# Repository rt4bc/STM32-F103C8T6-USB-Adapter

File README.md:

# STM32-F103C8T6-USB-Adapter
This hardware will be used as an adapter, expand GPIO, I2C, SPI and CAN interface via USB port.

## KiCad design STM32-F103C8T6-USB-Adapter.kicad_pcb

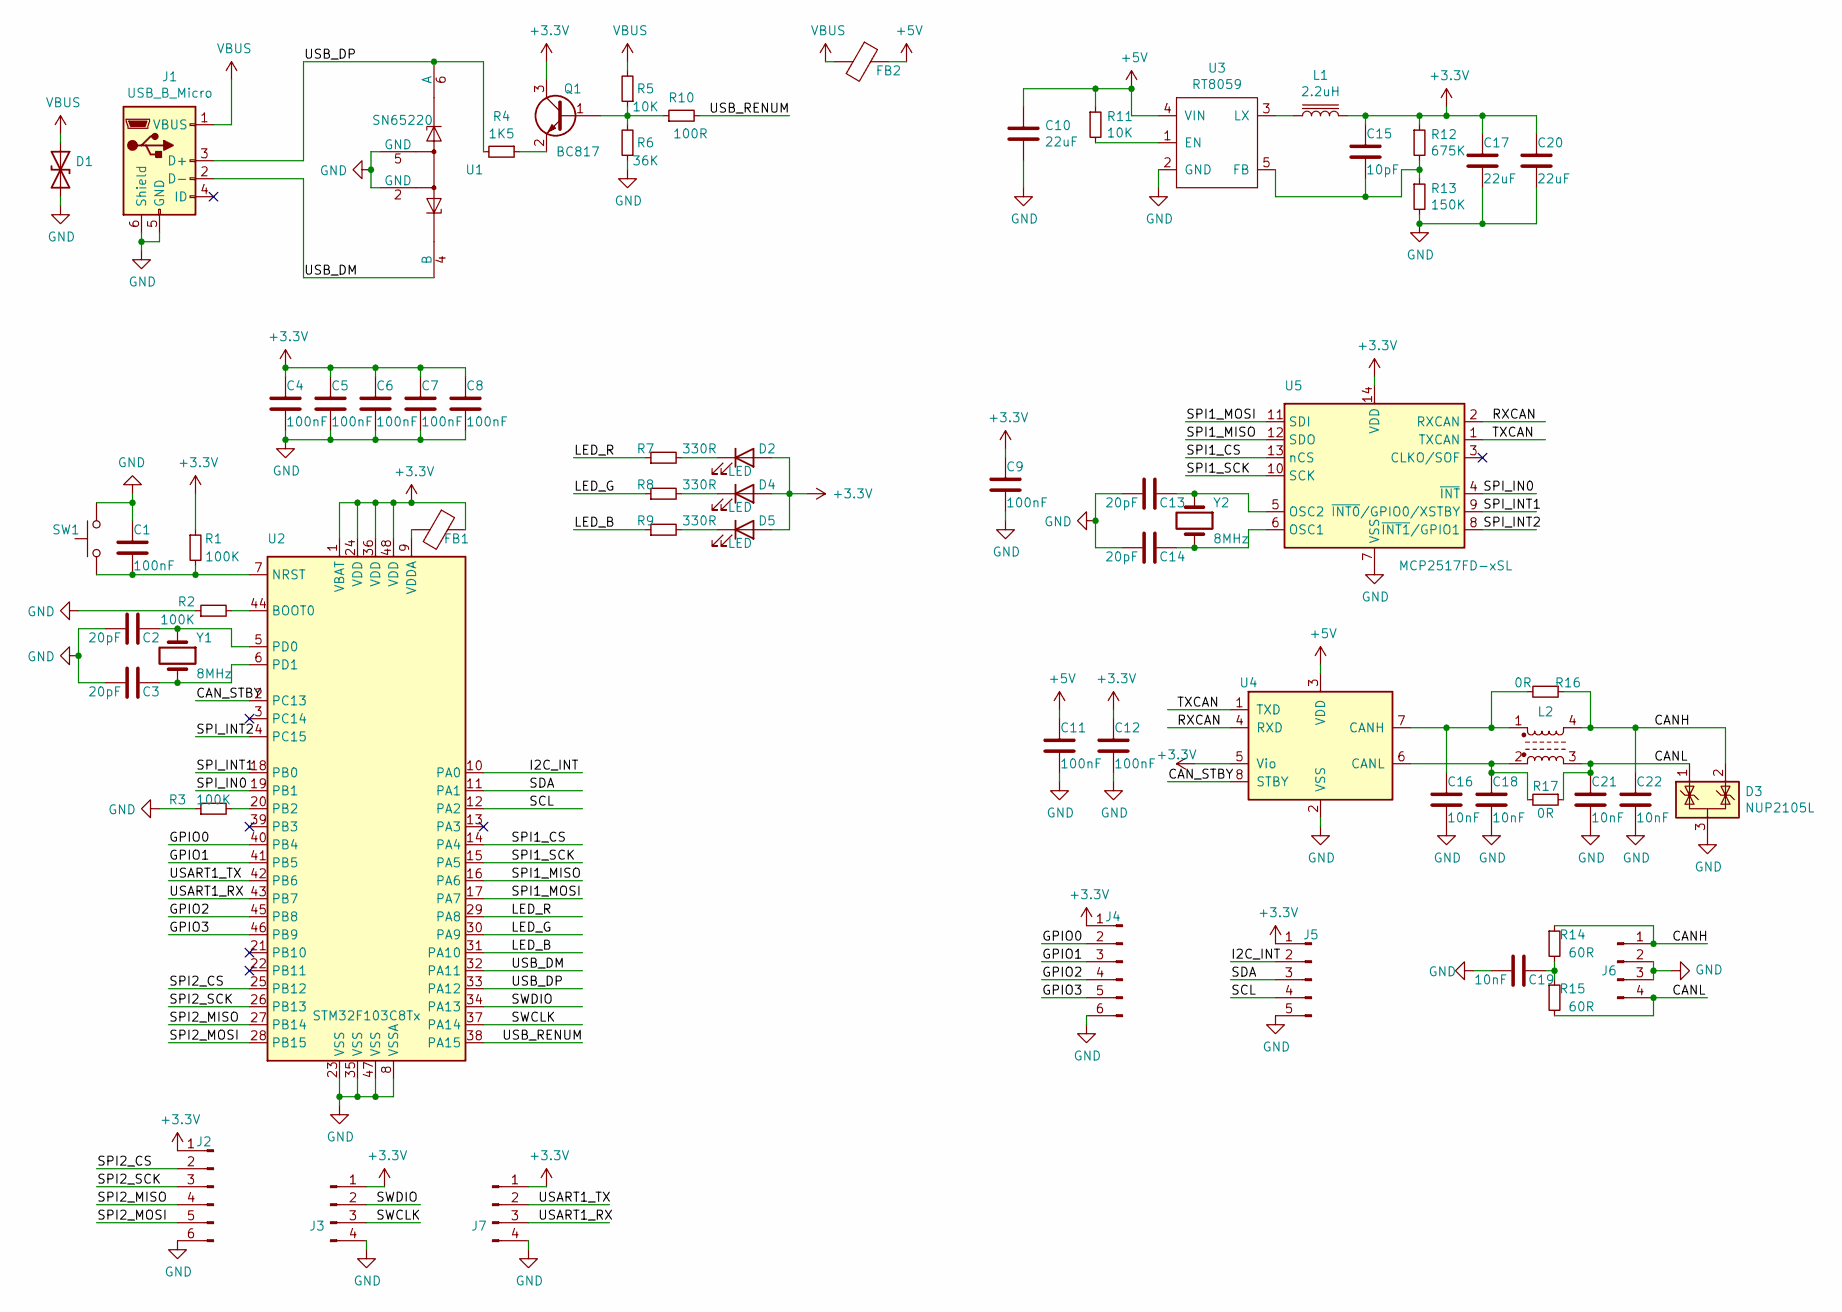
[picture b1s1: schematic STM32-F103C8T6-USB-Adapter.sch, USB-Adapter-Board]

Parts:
C1, C4, C5, C6, C7, C8, C9, C11, C12: 100nF; C_0603_1608Metric_Pad1.08x0.95mm_HandSolder
C2, C3, C13, C14: 20pF; C_0603_1608Metric_Pad1.08x0.95mm_HandSolder
C10, C17, C20: 22uF; C_0805_2012Metric_Pad1.18x1.45mm_HandSolder
C15: 10pF; C_0603_1608Metric_Pad1.08x0.95mm_HandSolder
C16, C18, C19, C21, C22: 10nF; C_0603_1608Metric_Pad1.08x0.95mm_HandSolder
D1: PESD5V0L1BA; D_SOD-323_HandSoldering
D2, D4, D5: LED; LED_0603_1608Metric_Pad1.05x0.95mm_HandSolder
D3: NUP2105L; SOT-23
FB1, FB2: Ferrite_Bead; L_0805_2012Metric_Pad1.05x1.20mm_HandSolder
J1: USB_B_Micro; USB_Mini-B_Wuerth_65100516121_Horizontal
J2, J4: Conn_01x06_Male; PinHeader_1x06_P2.54mm_Vertical
J3, J6, J7: Conn_01x04_Male; PinHeader_1x04_P2.54mm_Vertical
J5: Conn_01x05_Male; PinHeader_1x05_P2.54mm_Vertical
L1: 2.2uH; L_Vishay_IHLP-1212
L2: DR331-513; L_CommonModeChoke_Bourns_DR331
Q1: BC817; SOT-23
R1, R2, R3: 100K; R_0603_1608Metric_Pad0.98x0.95mm_HandSolder
R4: 1K5; R_0603_1608Metric_Pad0.98x0.95mm_HandSolder
R5, R11: 10K; R_0603_1608Metric_Pad0.98x0.95mm_HandSolder
R6: 36K; R_0603_1608Metric_Pad0.98x0.95mm_HandSolder
R7, R8, R9: 330R; R_0603_1608Metric_Pad0.98x0.95mm_HandSolder
R10: 100R; R_0603_1608Metric_Pad0.98x0.95mm_HandSolder
R12: 675K; R_0603_1608Metric_Pad0.98x0.95mm_HandSolder
R13: 150K; R_0603_1608Metric_Pad0.98x0.95mm_HandSolder
R14, R15: 60R; R_0603_1608Metric_Pad0.98x0.95mm_HandSolder
R16, R17: 0R; R_0603_1608Metric_Pad0.98x0.95mm_HandSolder
SW1: SW_Push; SW_SPST_B3U-1000P
U1: SN65220; SOT-23-6
U2: STM32F103C8Tx; LQFP-48_7x7mm_P0.5mm
U3: RT8059; SOT-23-5_HandSoldering
U4: MCP2562-E-SN; SOIC-8_3.9x4.9mm_P1.27mm
U5: MCP2517FD-xSL; SOIC-14_3.9x8.7mm_P1.27mm
Y1, Y2: 8MHz; Crystal_SMD_5032-2Pin_5.0x3.2mm_HandSoldering

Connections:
+3V3: C4.1, C5.1, C6.1, C7.1, C8.1, C9.1, C12.1, C15.1, C17.1, C20.1, D2.2 (A), D4.2 (A), D5.2 (A), FB1.1, J2.1, J3.1, J4.1, J5.1, J7.1, L1.2, Q1.3 (C), R1.1, R12.1, U2.1 (VBAT), U2.24 (VDD), U2.36 (VDD), U2.48 (VDD), U4.5 (Vio), U5.14 (VDD)
+5V: C10.1, C11.1, FB2.1, R11.1, U3.4 (VIN), U4.3 (VDD)
/CANH: C22.1, D3.2 (K), J6.1, L2.4, R14.1, R16.1
/CANL: C21.1, D3.1 (K), J6.4, L2.3, R15.2, R17.1
/CAN_STBY: U2.2 (PC13), U4.8 (STBY)
/GPIO0: J4.2, U2.40 (PB4)
/GPIO1: J4.3, U2.41 (PB5)
/GPIO2: J4.4, U2.45 (PB8)
/GPIO3: J4.5, U2.46 (PB9)
/I2C_INT: J5.2, U2.10 (PA0)
/LED_B: R9.1, U2.31 (PA10)
/LED_G: R8.1, U2.30 (PA9)
/LED_R: R7.1, U2.29 (PA8)
/RXCAN: U4.4 (RXD), U5.2 (RXCAN)
/SCL: J5.4, U2.12 (PA2)
/SDA: J5.3, U2.11 (PA1)
/SPI1_CS: U2.14 (PA4), U5.13 (nCS)
/SPI1_MISO: U2.16 (PA6), U5.12 (SDO)
/SPI1_MOSI: U2.17 (PA7), U5.11 (SDI)
/SPI1_SCK: U2.15 (PA5), U5.10 (SCK)
/SPI2_CS: J2.2, U2.25 (PB12)
/SPI2_MISO: J2.4, U2.27 (PB14)
/SPI2_MOSI: J2.5, U2.28 (PB15)
/SPI2_SCK: J2.3, U2.26 (PB13)
/SPI_IN0: U2.19 (PB1), U5.4 (~INT)
/SPI_INT1: U2.18 (PB0), U5.9 (~INT0~/GPIO0/XSTBY)
/SPI_INT2: U2.4 (PC15), U5.8 (~INT1~/GPIO1)
/SWCLK: J3.3, U2.37 (PA14)
/SWDIO: J3.2, U2.34 (PA13)
/TXCAN: U4.1 (TXD), U5.1 (TXCAN)
/USART1_RX: J7.3, U2.43 (PB7)
/USART1_TX: J7.2, U2.42 (PB6)
/USB_DM: J1.2 (D-), U1.4 (B), U2.32 (PA11)
/USB_DP: J1.3 (D+), R4.2, U1.6 (A), U2.33 (PA12)
/USB_RENUM: R10.2, U2.38 (PA15)
GND: C1.1, C2.2, C3.2, C4.2, C5.2, C6.2, C7.2, C8.2, C9.2, C10.2, C11.2, C12.2, C13.2, C14.2, C16.2, C17.2, C18.2, C19.2, C20.2, C21.2, C22.2, D1.2 (A2), D3.3 (A), J1.5 (GND), J1.6 (Shield), J2.6, J3.4, J4.6, J5.5, J6.2, J6.3, J7.4, R2.1, R3.1, R6.1, R13.2, SW1.2, U1.2 (GND), U1.5 (GND), U2.8 (VSSA), U2.23 (VSS), U2.35 (VSS), U2.47 (VSS), U3.2 (GND), U4.2 (VSS), U5.7 (VSS)
unnamed: C1.2, R1.2, SW1.1, U2.7 (NRST)
unnamed: C2.1, U2.5 (PD0), Y1.1
unnamed: C3.1, U2.6 (PD1), Y1.2
unnamed: C13.1, U5.5 (OSC2), Y2.1
unnamed: C14.1, U5.6 (OSC1), Y2.2
unnamed: C15.2, R12.2, R13.1, U3.5 (FB)
unnamed: C16.1, L2.1, R16.2, U4.7 (CANH)
unnamed: C18.1, L2.2, R17.2, U4.6 (CANL)
unnamed: C19.1, R14.2, R15.1
unnamed: D2.1 (K), R7.2
unnamed: D4.1 (K), R8.2
unnamed: D5.1 (K), R9.2
unnamed: FB1.2, U2.9 (VDDA)
unnamed: L1.1, U3.3 (LX)
unnamed: Q1.1 (B), R5.1, R6.2, R10.1
unnamed: Q1.2 (E), R4.1
unnamed: R2.2, U2.44 (BOOT0)
unnamed: R3.2, U2.20 (PB2)
unnamed: R11.2, U3.1 (EN)
VBUS: D1.1 (A1), FB2.2, J1.1 (VBUS), R5.2

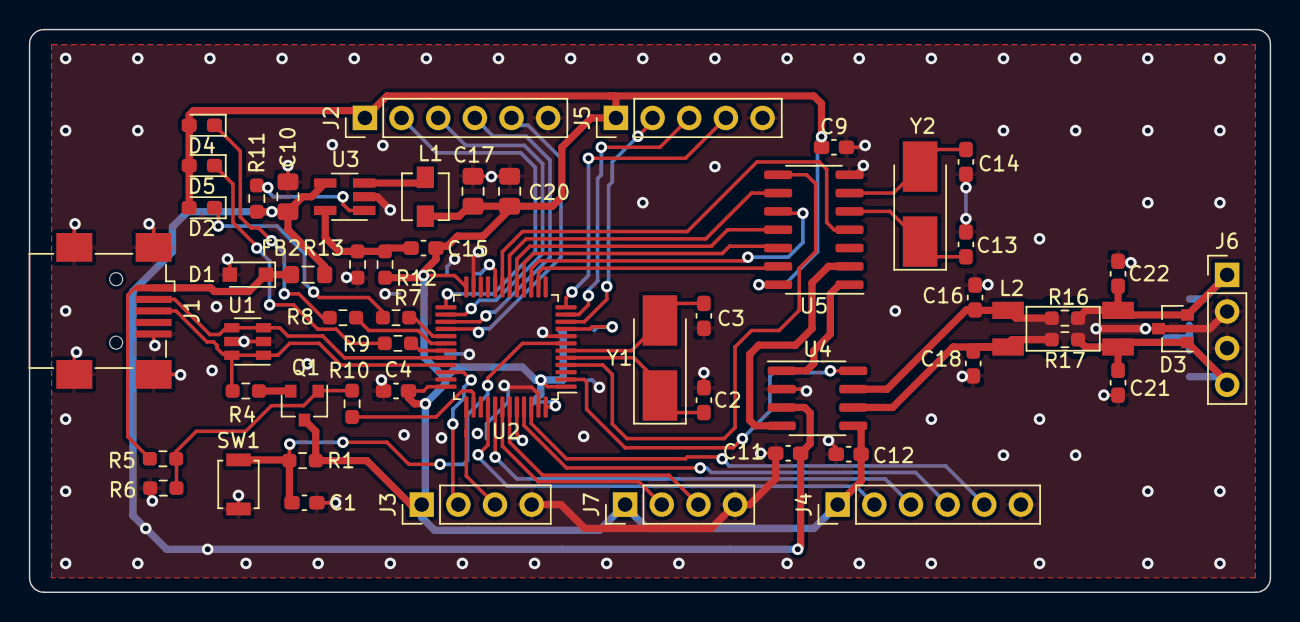
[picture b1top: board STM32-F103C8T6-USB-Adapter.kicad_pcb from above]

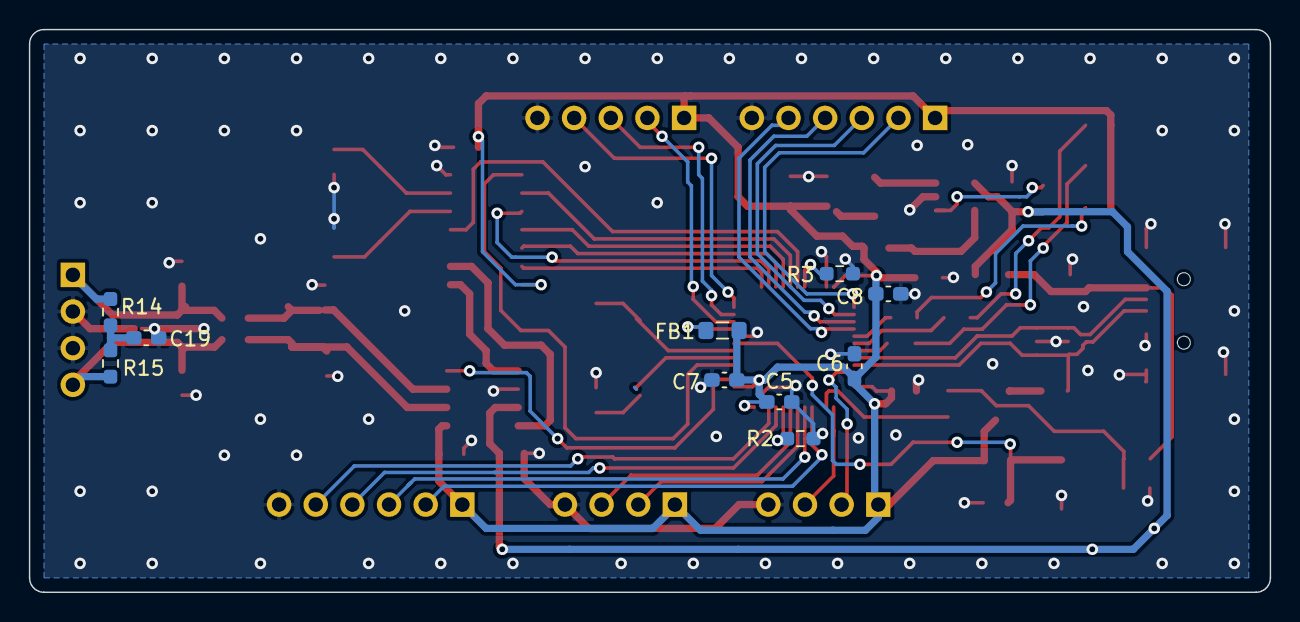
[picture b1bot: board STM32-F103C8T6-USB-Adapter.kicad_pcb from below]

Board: 2 copper layers, 86.0 x 39.0 mm, 64 parts (10 on the bottom side), 56 nets.

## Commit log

2020-12-14 add new files
2020-12-15 add chamfer on pcb corner
2020-12-15 add 3D view
2020-12-15 update 3d view
2020-12-15 optimize via of gnd copper
